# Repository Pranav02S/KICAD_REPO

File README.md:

View this project on [CADLAB.io](https://cadlab.io/project/29206). 

# KICAD_REPO

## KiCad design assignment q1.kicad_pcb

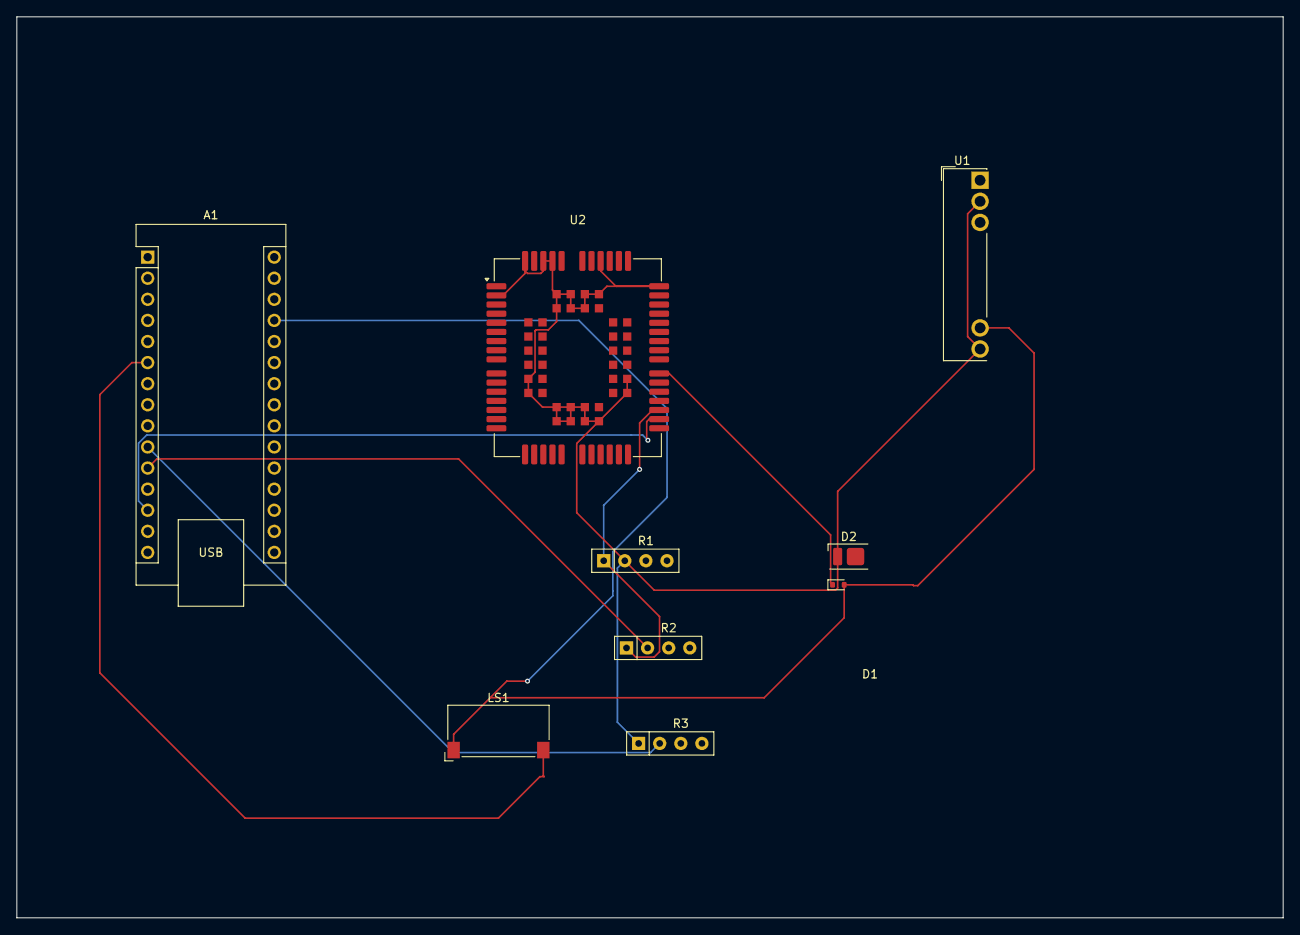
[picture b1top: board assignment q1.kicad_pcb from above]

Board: 2 copper layers, 152.5 x 108.5 mm, 9 parts (0 on the bottom side), 8 nets.

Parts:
A1: Arduino_Nano_v3.x; Arduino_Nano
D1: 1N4148WT; D_SOD-523
D2: LED_GRBK; LED_Everlight-SMD3528_3.5x2.8mm_67-21ST
LS1: Speaker_Ultrasound; Speaker_CUI_CMR-1206S-67
R1, R2, R3: R; R_Array_SIP4
U1: TOS06-05SIL; Converter_DCDC_TRACO_TOS06-05SIL_THT
U2: BC95; Quectel_BC95

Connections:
+5V: A1.27 (+5V), D1.2 (A), LS1.1, U1.4 (+Vin)
GND: D2.1 (GA), R1.2, R3.1, U1.2 (Trim), U1.5 (ON/~OFF), U2.2 (GND), U2.43 (GND), U2.47 (GND), U2.48 (GND), U2.51 (GND), U2.52 (GND), U2.54 (GND), U2.59 (GND), U2.60 (GND), U2.61 (GND), U2.62 (GND), U2.63 (GND), U2.64 (GND), U2.65 (GND), U2.66 (GND), U2.71 (GND), U2.72 (GND), U2.73 (GND), U2.74 (GND), U2.81 (GND), U2.82 (GND), U2.83 (GND), U2.92 (GND), U2.93 (GND), U2.94 (GND)
unnamed: A1.6 (D3), LS1.2
unnamed: A1.10 (D7), R3.2
unnamed: A1.11 (D8), R2.2
unnamed: A1.13 (D10), U2.29 (RXD)
unnamed: D1.1 (K), U2.34 (RI)
unnamed: R1.1, R2.1, U2.30 (TXD)

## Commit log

2025-04-02 kicad project
2025-04-09 Backlink to CADLAB.io has been added.
2026-02-18 Created using Colab
